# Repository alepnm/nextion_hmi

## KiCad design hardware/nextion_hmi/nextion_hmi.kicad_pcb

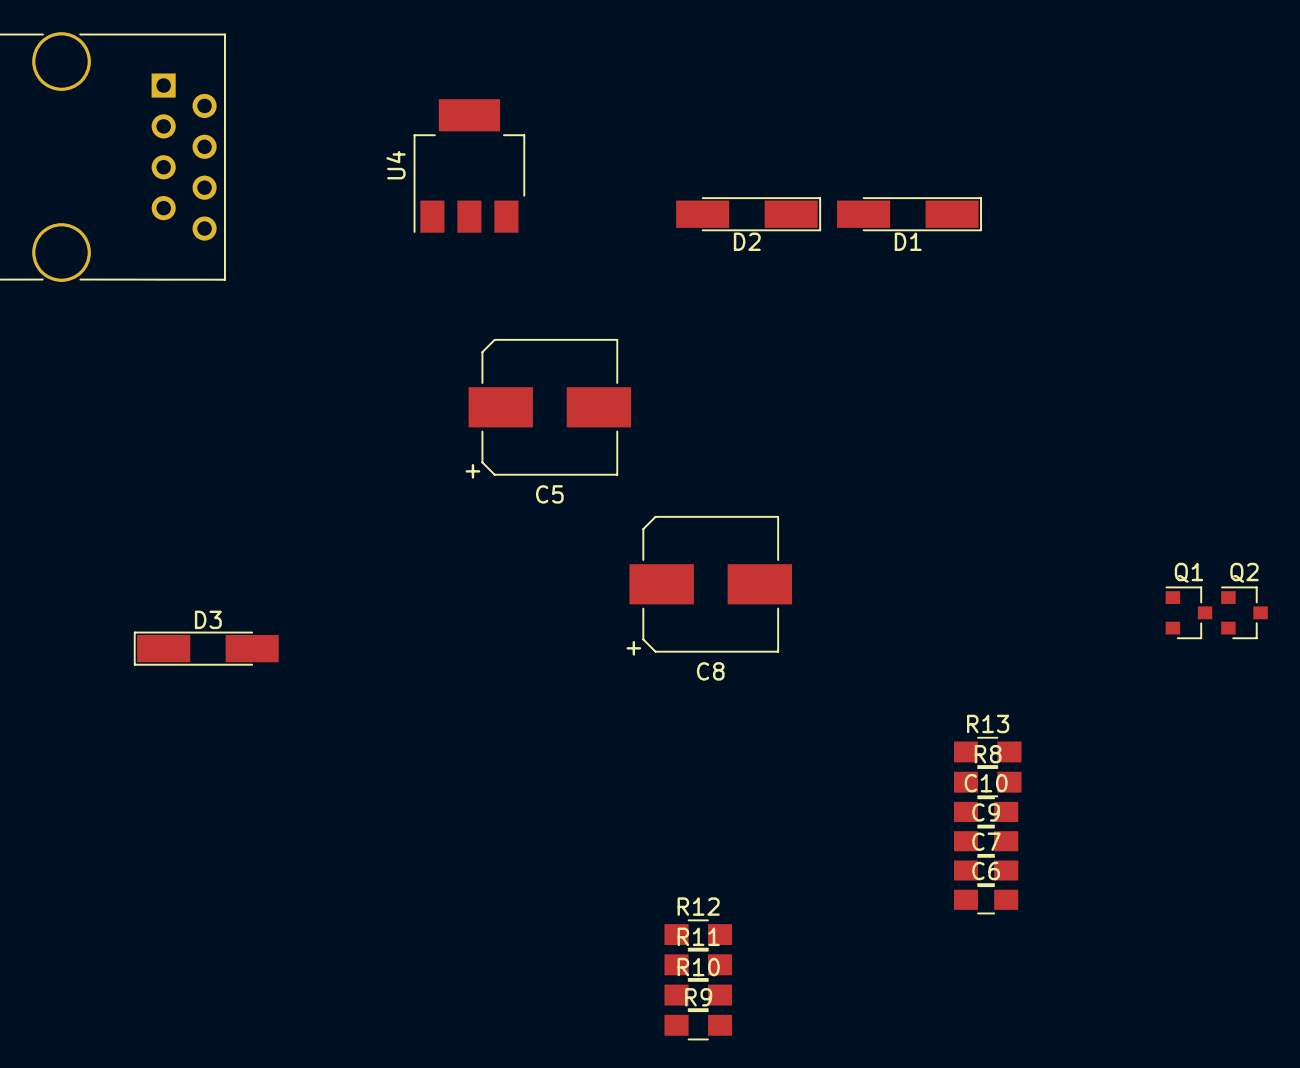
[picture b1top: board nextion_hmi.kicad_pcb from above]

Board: 2 copper layers, 19 parts (0 on the bottom side), 11 nets, no tracks yet.

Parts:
C5, C8: 100,0x16V; CP_Elec_8x10
C6, C7, C9: 100nF; C_0805_HandSoldering
C10: 1nF; C_0805_HandSoldering
D1, D2, D3: BAS85; D_MiniMELF_Handsoldering
J3: RJ45_Shielded; RJ45_8
Q1, Q2: BC817; SOT-23
R8, R11: 10k; R_0805_HandSoldering
R9, R10: 1k0; R_0805_HandSoldering
R12: 100; R_0805_HandSoldering
R13: 5k1; R_0805_HandSoldering
U4: LM340-5.0-SMD; SOT-223-3_TabPin2

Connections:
/12VDC: C5.1, C6.1, C9.1, J3.7, J3.8, R11.2, U4.1
/DATA: J3.5, R12.1
/GND: C5.2, C6.2, C7.2, C8.2, C9.2, C10.2, J3.1, J3.2, Q1.2, Q2.2, U4.2
/UART konverteris/5VDC: C7.1, C8.1, D2.2, U4.3
unnamed: C10.1, Q1.3, R8.1, R9.1
unnamed: D1.1, R8.2
unnamed: D1.2, D2.1
unnamed: D3.1, R10.2
unnamed: D3.2, Q2.3, R11.1, R12.2
unnamed: Q1.1, R10.1
unnamed: Q2.1, R13.1

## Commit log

2018-08-02 projekto inicializavimas
2018-08-02 tarpinis komitas
2018-08-03 datasheetai komponentams
2018-08-03 lcd funkcionalumo aprasymas. veikia isorine flash atmintis, touch kontroleris, kitos funkcijos
2018-08-03 papildyta datashitais ir kita info
2018-08-07 tarpinis kommitas
2018-08-07 veikia pagrindines lcd funkcijos
2018-08-08 tft lcd funkcionalumo realizacija
2018-08-09 fatfs stekas darbui su sd kortele. kompiliuojasi be klaidu. reikia tikrinti
2018-08-09 lcd write bitmap kodavimas
2018-08-10 extern flash funkciju rasymas
2018-09-13 flash spi ir microsd prijungimas
2018-09-14 prijungtas ekzamplinis nucleo projektas - lcd, sd, fat... kompiliuojasi, bet truksta ramo...
2018-09-17 keiciama projekto struktura. tarpinis kommitas
2018-11-19 schemos paruosimas
